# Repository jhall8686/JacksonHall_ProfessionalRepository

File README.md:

# JacksonHall_ProfessionalRepository

This repository will contain CAD, code, and Images from the projects I have completed throughout my career.

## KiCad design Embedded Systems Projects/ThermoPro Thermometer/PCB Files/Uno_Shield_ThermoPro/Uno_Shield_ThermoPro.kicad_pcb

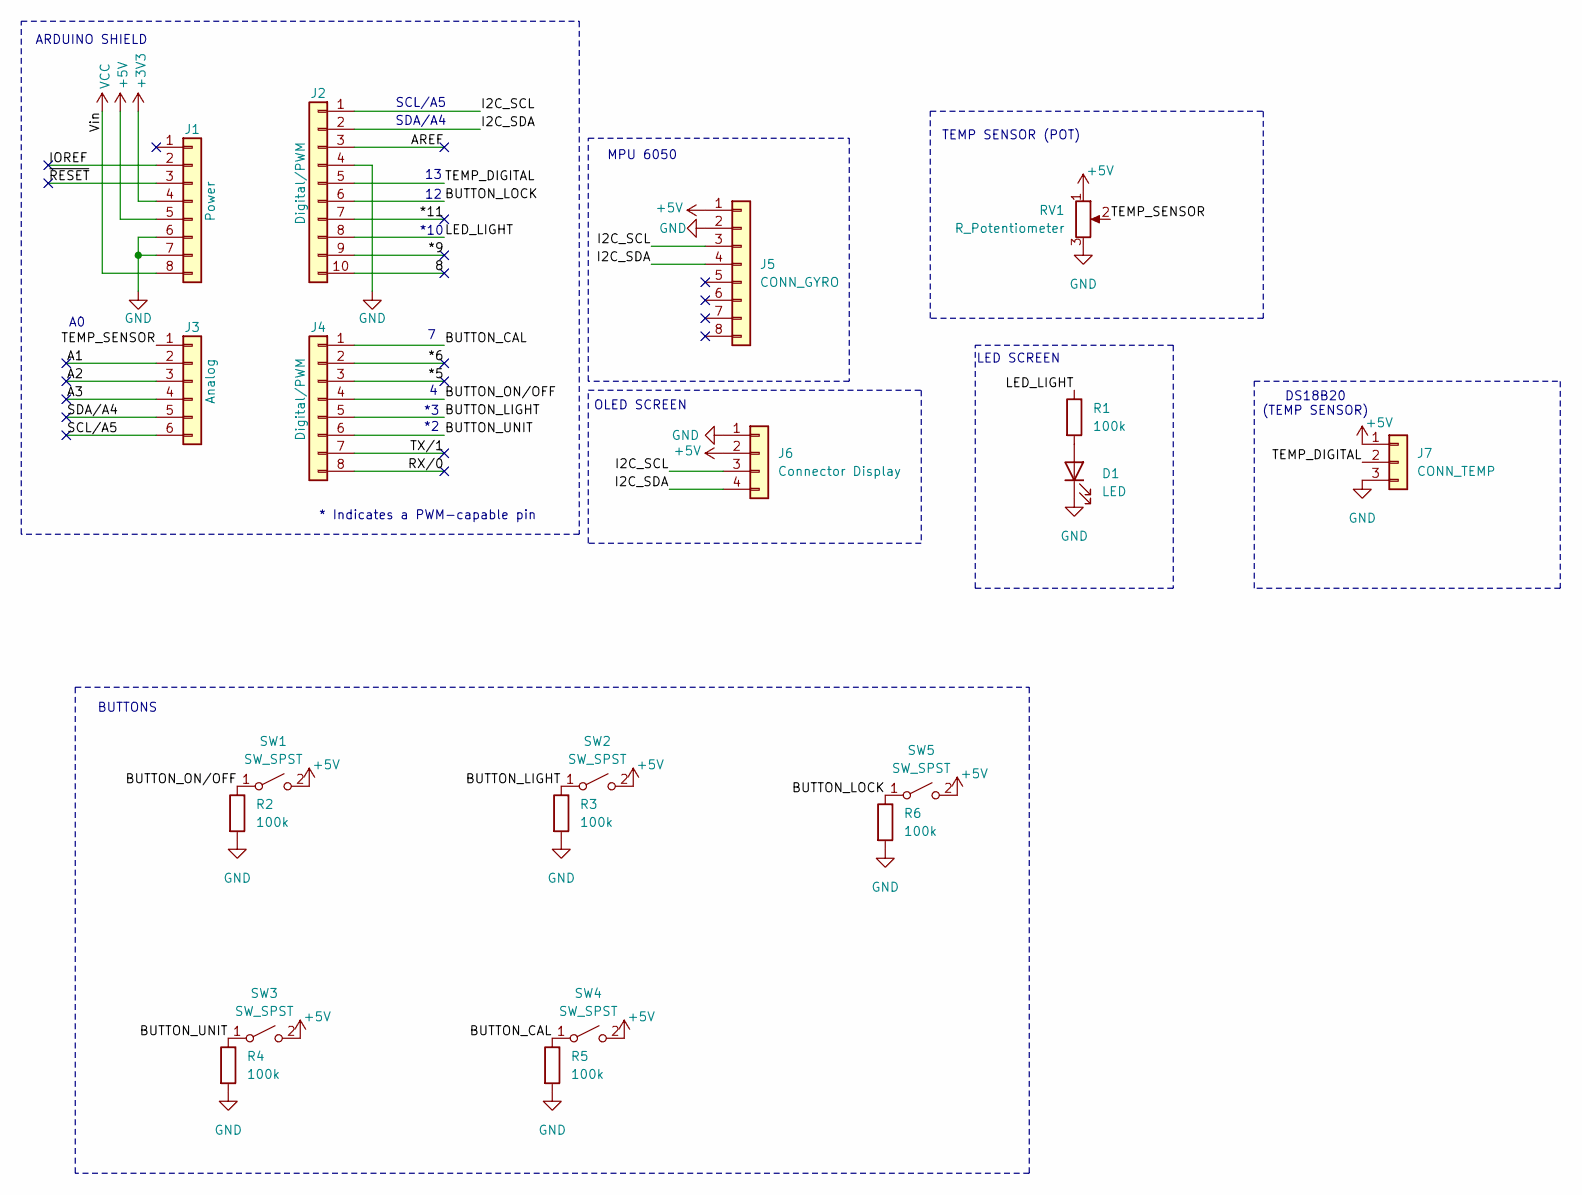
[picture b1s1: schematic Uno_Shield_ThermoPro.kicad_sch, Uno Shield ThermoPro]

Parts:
D1: LED; LED_D5.0mm
J1: Power; PinSocket_1x08_P2.54mm_Vertical
J2: Digital/PWM; PinSocket_1x10_P2.54mm_Vertical
J3: Analog; PinSocket_1x06_P2.54mm_Vertical
J4: Digital/PWM; PinSocket_1x08_P2.54mm_Vertical
J5: CONN_GYRO; PinSocket_1x08_P2.54mm_Vertical
J6: Connector Display; PinSocket_1x04_P2.54mm_Vertical
J7: CONN_TEMP; JST_XH_B3B-XH-A_1x03_P2.50mm_Vertical
R1, R2, R3, R4, R5, R6: 100k; R_Axial_DIN0207_L6.3mm_D2.5mm_P10.16mm_Horizontal
RV1: R_Potentiometer; Potentiometer_Bourns_3386P_Vertical
SW1, SW2, SW3, SW4, SW5: SW_SPST; SW_PUSH_6mm

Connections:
+3V3: J1.4
+5V: J1.5, J5.1, J6.2, J7.1, RV1.1, SW1.2 (B), SW2.2 (B), SW3.2 (B), SW4.2 (B), SW5.2 (B)
/8: J2.10
/*5: J4.3
/*6: J4.2
/*9: J2.9
/*11: J2.7
/A1: J3.2
/A2: J3.3
/A3: J3.4
/AREF: J2.3
/BUTTON_CAL: J4.1, R5.1, SW4.1 (A)
/BUTTON_LIGHT: J4.5, R3.1, SW2.1 (A)
/BUTTON_LOCK: J2.6, R6.1, SW5.1 (A)
/BUTTON_ON/OFF: J4.4, R2.1, SW1.1 (A)
/BUTTON_UNIT: J4.6, R4.1, SW3.1 (A)
/I2C_SCL: J2.1, J5.3, J6.3
/I2C_SDA: J2.2, J5.4, J6.4
/IOREF: J1.2
/LED_LIGHT: J2.8, R1.1
/RX/0: J4.8
/SCL/A5: J3.6
/SDA/A4: J3.5
/TEMP_DIGITAL: J2.5, J7.2
/TEMP_SENSOR: J3.1, RV1.2
/TX/1: J4.7
/~RESET: J1.3
GND: D1.1 (K), J1.6, J1.7, J2.4, J5.2, J6.1, J7.3, R2.2, R3.2, R4.2, R5.2, R6.2, RV1.3
unnamed: D1.2 (A), R1.2
VCC: J1.8

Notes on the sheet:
MPU 6050
DS18B20 (TEMP SENSOR)
SDA/A4
*10
BUTTONS
ARDUINO SHIELD
LED SCREEN
* Indicates a PWM-capable pin
TEMP SENSOR (POT)
SCL/A5
OLED SCREEN

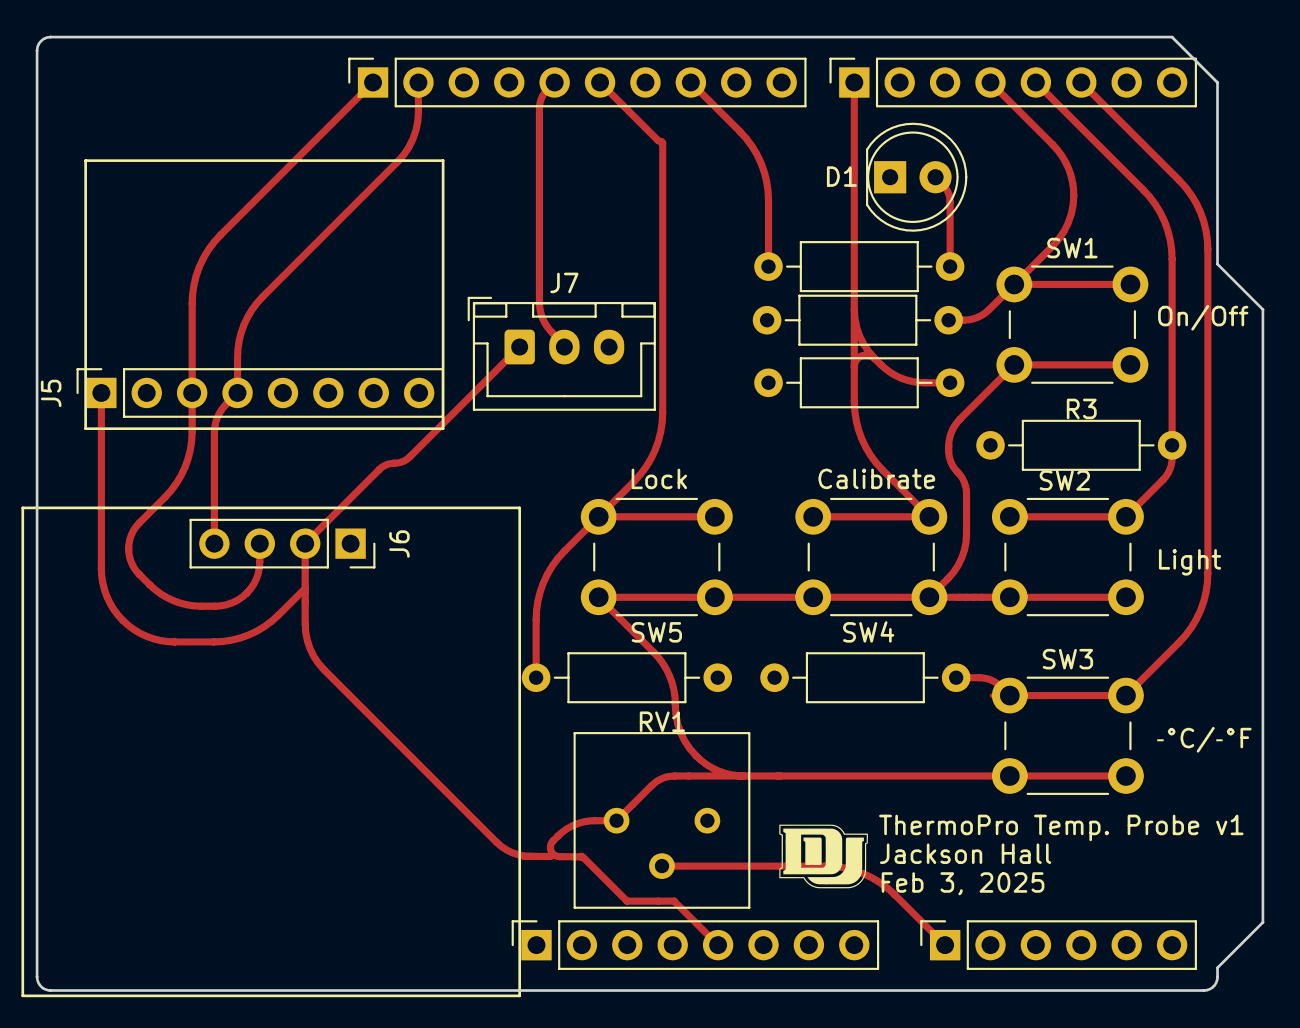
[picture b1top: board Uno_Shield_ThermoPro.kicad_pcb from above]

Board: 2 copper layers, 68.6 x 53.3 mm, 20 parts (0 on the bottom side), 13 nets.

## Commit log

2025-04-29 Init Repository
